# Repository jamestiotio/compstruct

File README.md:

# compstruct

_"From Transistors to the Operating System."_

_"If you wish to print('Hello World') from scratch, you must first invent the entire universe."_

SUTD 2020 50.002 Computation Structures Code Dump

## Future Addons

- Implement a one-round partial/half DES encryption algorithm on a 32-bit plaintext (and a 32-bit key) and verify the ciphertext by using BSim on the Beta simulator. It will not be a full triple-DES, 16-rounds-each implementation, but for the sake of a model demonstration as in this case, it should be fine.
- Implement a general-purpose 32-bit CPU processor architecture, complete with its own associated memory unit in Lucid (or Verilog).
- Add demo program of a method to draw animations/videos frame-by-frame on the BSim render window.

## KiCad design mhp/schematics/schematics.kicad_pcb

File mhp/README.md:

# 50.002 1D Part 1: Mini Hardware Project

SUTD ISTD 2020 Computation Structures Mini Hardware Project: 1-Bit Full Adder & FPGA Tester.

Team 03-2:

- [James Raphael Tiovalen](https://github.com/jamestiotio) (Team Leader)
- [Ng Yu Yan](https://github.com/ngyy3487)
- [Sun Kairan](https://github.com/kairanskrr)
- [Cheow Wei Da Nicholas](https://github.com/nicholascwd)
- Jodi Tan Kai Yu

[Poster](poster.pdf) and [schematics](schematics/schematics.png) are included in this repository. You can watch our video [here](https://youtu.be/cUwy_Xbg1K8).

---

For the FPGA Tester, we are using the standard library's `io.acf` provided by Xilinx Vivado, so we do not need to define any custom `.acf` file(s).

To start testing the 1-Bit Full Adder, connect the circuit to the provided VDD (+3.3 Volts) and GND on the custom-made SUTD ISTD Alchitry Br PCB board (any bank). And then, connect the output Sum Bit wire to B42 and output Carry-Out Bit wire to B43. Turn off the switches on the Alchitry IO board for `io_dip[2][2:0]` and `io_dip[1][1:0]`. `io_led[2][2:0]` will serve as input LEDs (thus indicating the values of A, B and C_in) and `io_led[1][1:0]` will serve as output LEDs (thus indicating the values of S and C_out).

There are 2 modes of testing:

- Manual

  Ensure that `io_dip[0][0]` is turned off (switched to LOW). We utilize the 1-Bit Full Adder's own DIP switch (in its own circuit) for manual mode. Connect the input wires A, B and Carry-In to pins A33, A31 and A30 respectively. Power up the FPGA or press the Reset button on the Alchitry Au board. Manually turn off or on the switch on the 1-Bit Full Adder circuit. The input LEDs on the FPGA should correspond to the output LEDs. If so, press the CENTER button on the IO Shield to check the result (it will display two dots  in the middle). If successful, the circulating animation will also remain since we are still in testing mode. If the check fails, the 4 7-segment displays will show a "FAIL". Once you have gone through all 8 test cases, press the UP button on the IO Shield to finish the manual checking test. It will show a "PASS" if you managed to not "FAIL" any test cases.

- Automatic

  Ensure that `io_dip[0][0]` is turned on (switched to HIGH). We utilize the FPGA's internal circuitry to send clock-governed signals to the external 1-Bit Full Adder circuit. Connect the input wires A, B and Carry-In to pins A18, A20 and A21 respectively. Also ensure that ALL of the 4 switches on the DIP switch on the 1-Bit Full Adder circuit is switched off (or else, the automatic check will fail since the signals would be overridden by the in-circuit switch). Power up the FPGA or press the Reset button on the Alchitry Au board. The code will cycle through all 8 entries of the truth table. Wait for the result to be shown on the 4 7-segment displays, which is either a "FAIL" or a "PASS".

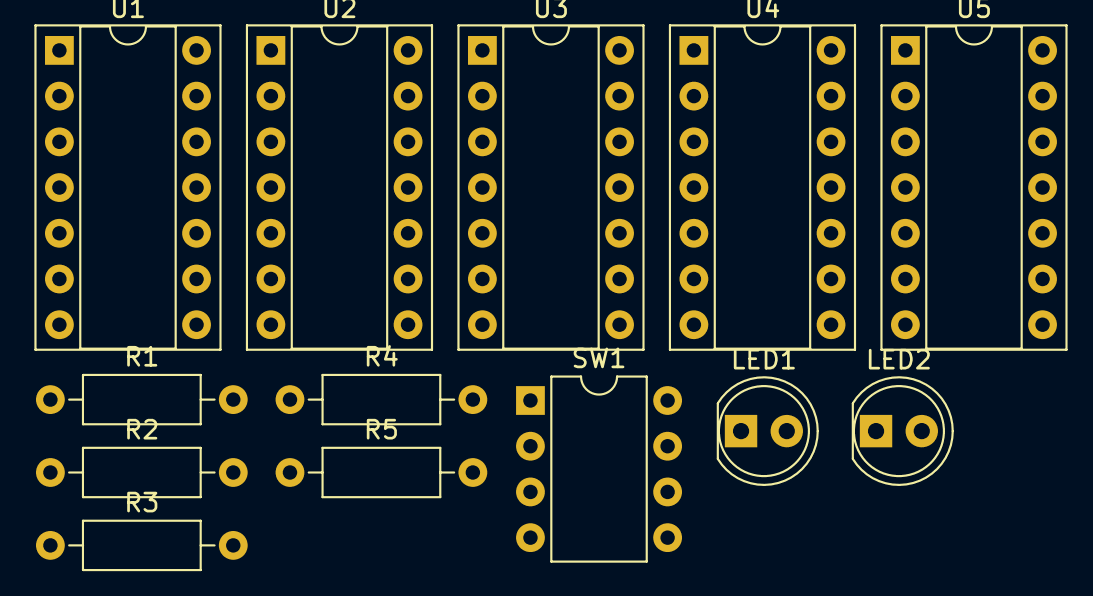
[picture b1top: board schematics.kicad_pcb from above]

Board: 2 copper layers, 13 parts (0 on the bottom side), 12 nets, no tracks yet.

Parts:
LED1, LED2: LED; LED_D5.0mm
R1, R2: 470Ω; R_Axial_DIN0207_L6.3mm_D2.5mm_P10.16mm_Horizontal
R3, R4, R5: 12kΩ; R_Axial_DIN0207_L6.3mm_D2.5mm_P10.16mm_Horizontal
SW1: SW_DIP_x04; DIP-8_W7.62mm
U1, U2: CD74HC86E; DIP-14_W7.62mm_Socket
U3, U4: SN74HC08N; DIP-14_W7.62mm_Socket
U5: SN74HC32N; DIP-14_W7.62mm_Socket

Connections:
/A: R3.2, SW1.8, U1.1, U4.1
/B: R4.2, SW1.7, U1.2, U4.2
/Cin: R5.2, SW1.6, U2.2, U3.1
/Cout: LED2.2, R2.1
/FPGA/+3.3V: SW1.1, SW1.2, SW1.3
/S: LED1.2, R1.1
GND: LED1.1, LED2.1, R3.1, R4.1, R5.1
unnamed: R1.2, U2.3
unnamed: R2.2, U5.3
unnamed: U1.3, U2.1, U3.2
unnamed: U3.3, U5.1
unnamed: U4.3, U5.2

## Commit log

2020-09-19 Add .whitesource configuration file
2020-09-24 Add lab1 file & library dependencies
    Note that gates.jsim is custom-made (not from original SUTD/MIT source files).
2020-10-01 Add lab2 code
2020-10-10 Add Mini Hardware Project files
2020-10-10 [ImgBot] Optimize images
    /mhp/schematics/schematics.png -- 55.13kb -> 14.29kb (74.09%)
2020-10-11 Add FPGA tester as a block to circuit diagram
2020-10-11 Neaten whitespace & add FSM
2020-10-11 Add latest schematics image
2020-10-11 [ImgBot] Optimize images
    /mhp/schematics/schematics.png -- 66.22kb -> 16.49kb (75.1%)
2020-10-11 Add poster, schematics link and video link
2020-10-25 Add lab3 code
2020-10-25 Add more comment for lab3 code
2020-10-25 Add slight change to comment on Python script
    Change "\n" to "" to prevent double newlines
2020-10-27 Improve implementation of overflow bit
    Optimized version has slightly better area-delay product (less gates used, faster speed)
2020-10-29 Add submodule
2020-11-04 Update submodule
2020-11-05 Update EHP submodule
2020-11-17 Add Lab 4 & 5 solutions
2020-11-17 Update lab5 comments
2020-11-18 Remove illegal Unicode characters
    This is to prevent the "incorrect string value for column circuits at row 1" error so that a successful checkoff login is executed.
    Before implementing this, checkoff verification is still successful. However, login will still fail if there are illegal Unicode characters present.
2020-11-19 Change all SXT to SEXT to indicate Sign Extension
2020-11-19 Update comments
2020-11-19 Add equivalent name of pcbig
2020-11-20 Remove duplicate sign extension procedure
2020-11-20 Slightly improve some comments
2020-11-23 Add labs 6-8 starter codes
2020-11-23 Update lab6 C implementation
2020-11-28 Add Lab 6 solution
2020-12-07 Add KiCad gitignore
2020-12-09 Improve modularity of lab5 solution
2020-12-09 Fix grammar
2020-12-11 Add lab8 solutions & update submodule
2020-12-11 Add more lab8 solutions
    Follow original lab handout specifications
2020-12-13 Update lab8 & ehp submodule
2020-12-14 Add lab7 solutions
2020-12-15 Reformat whitespace in lab8
2020-12-15 Remove some tabs from lab8
2020-12-18 Add more comments to lab7 for better explanation
2020-12-22 Update team member list with Github profile account links
2021-01-25 Fix indentation of lab7
2021-04-27 Update README with more future TODOs
2021-06-01 Update README with tagline
2022-01-18 Add new README tagline
2022-01-20 Update lab 6 comment
2022-02-10 Add lab 1 comments
2022-02-24 Add comments to test lab 3 ALU sub-components
2022-02-24 Add Beta control unit ROM table
2022-02-24 [ImgBot] Optimize images
    /labs/CU_2.png -- 112.37kb -> 39.08kb (65.22%)
2022-04-07 Remove useless whitespace from lab 6 solution
